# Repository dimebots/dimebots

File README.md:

Dimebots are a collection of autonomous and self-contained micro-robots that are as small as a dime and weigh less than a nickel, making Dimebots some of the smallest robots in the world. 

<p><strong>Microchip/Atmel ATTiny1614 &amp; Texas Instruments DRV8837</strong></p>

<p>The search for a suitable microcontroller is constrained by a number 
of factors. These factors included providing the necessary peripherals 
that are required, such as <a href="https://en.wikipedia.org/wiki/Pulse-width_modulation" target="_blank" rel="noreferrer noopener">Pulse Width Modulation (PWM)</a>, at least one <a href="https://en.wikipedia.org/wiki/Universal_asynchronous_receiver-transmitter" target="_blank" rel="noreferrer noopener">Universal Asynchronous Receiver/Transmitter (UART)</a>, support for at least one Inter-Integrated Circuit <a href="https://en.wikipedia.org/wiki/I%C2%B2C" target="_blank" rel="noreferrer noopener">(I²C)</a> communication bus, and in-circuit serial programming <a href="https://ww1.microchip.com/downloads/en/DeviceDoc/30277d.pdf" target="_blank" rel="noreferrer noopener">(ICSP)</a>. I originally designed the Dimebots to utilized the 8-bit <a href="https://www.microchip.com/en-us/product/ATmega328P" target="_blank" rel="noreferrer noopener">Microchip/Atmel ATmega328p</a> which is the microcontroller found in the <a href="https://www.arduino.cc/" target="_blank" rel="noreferrer noopener">Arduino Uno</a>.
 The ATmega328p provides a simple and easy-to-understand coding platform
 through the Arduino integrated development environment (IDE) while also
 coming in a number of footprints that could work for my requirements, 
namely a 32 pin <a href="https://en.wikipedia.org/wiki/Quad_flat_package" target="_blank" rel="noreferrer noopener">Thin Quad Flat Package (TQFP)</a> and 28 and 32 pin <a href="https://en.wikipedia.org/wiki/Flat_no-leads_package" target="_blank" rel="noreferrer noopener">Very Thin Plastic Quad Flat No-Lead (VQFN)</a>. I went as far as laying out an <a href="https://www.microchip.com/en-us/product/ATmega328P" target="_blank" rel="noreferrer noopener">ATMega328p</a>
 using a VQFN footprint, but the additional support requirements of 
using the ATMega328p such as a 6 pin ICSP header and an external 8MHz 
crystal/resonator necessitated a smaller microcontroller. In addition, 
the great dearth of microchips because of the COVID-19 pandemic 
disrupting global supply chains, stay-at-home orders increasing, and 
demand for consumer electronics and electric vehicle adoption, such as 
the ATMega328p, makes my selection of a suitable microcontroller much 
narrower. I decided to give myself a couple of weeks to see if I could 
nail down a microcontroller that is small, yet peripheral rich. 
Fortunately, <a href="https://github.com/SpenceKonde/megaTinyCore" target="_blank" rel="noreferrer noopener">Spence Konde (aka Dr. Azzy)</a>
 had recently released Arduino support for the newer microcontrollers 
offered by Microchip/Atmel, including support for the tinyAVR 2-Series, 
the tinyAVR 1-Series, and the tinyAVR 0-Series of chips. After testing a
 number of different microcontrollers, I chose the <a href="https://www.microchip.com/en-us/product/ATTINY1614" target="_blank" rel="noreferrer noopener">ATTiny1614</a> in a 14-pin <a href="https://en.wikipedia.org/wiki/Small_outline_integrated_circuit" target="_blank" rel="noreferrer noopener">Small Outline Integrated Circuit (SOIC)</a>
 footprint due to its necessary peripherals, overall microcontroller 
size and footprint, and most importantly, its availability. The 
ATTiny1614 can be powered by a wide variety of voltages including 1.8V 
all the way up to 5.5, has multiple I²C buses and multiple UART’s, has 6
 PWM channels, and used the <a href="https://onlinedocs.microchip.com/pr/GUID-DDB0017E-84E3-4E77-AAE9-7AC4290E5E8B-en-US-4/index.html?GUID-9B349315-2842-4189-B88C-49F4E1055D7F" target="_blank" rel="noreferrer noopener">Unified Program and Debug Interface (UPDI)</a>
 for programming. The UPDI interface is perfect for my needs, as it 
required only a 3-pin programming interface versus the 6-pin interface 
used for the ATMega328p.</p>

<p>The <a href="https://www.ti.com/product/DRV8837" target="_blank" rel="noreferrer noopener">Texas Instruments DRV8837</a>
 is chosen as the motor driver for the Dimebots. The DRV8837 output 
driver block consists of N-channel power MOSFETs configured as an 
H-bridge to drive the motor winding. An internal charge pump generates 
needed gate drive voltages. The Texas Instruments DRV8837 is packaged 
with a host of features, namely:</p>

<ul>
<li>1.8-A Maximum Drive Current</li>
<li>Separate Motor and Logic Supply Pins</li>
<li>Motor VM: 0 to 11 V</li>
<li>Logic VCC: 1.8 to 7 V</li>
<li>PWM Interface with IN1 and IN2 receiving PWM input</li>
<li>Low-Power Sleep Mode With 120-nA Maximum Sleep Current</li>
<li>nSLEEP pin</li>
<li>Small Footprint – 8-Pin WSON With Thermal Pad with a 2.0mm × 2.0mm size</li>
</u!>

<p><strong>Vishay VCNL4040 Proximity Sensor</strong></p>

<p>I sampled and tested numerous proximity sensors to find one that is power friendly, small, and available. This included sensors such as the Broadcom APDS-9960, the ON Semiconductor QRE1113, and the Sharp GP2S60. I finally selected the VCNL4040 from Vishay that interfaced with the ATTiny1614 using the I²C protocol.</p>

<p><strong>Nanjing Qinheng Microelectronics CH9141 Bluetooth (BLE4.2) Module</strong></p>

<p>Searching for a Bluetooth LE module that is tiny enough to fit the constraints of the robots mainboard while also providing for some type of serial communications is a challenge. All of the traditional Bluetooth 2.0 Serial Port Profile (SPP) modules were either too large or too power hungry to meet the dime-sized requirements of the Dimebots. After a few weeks of exhaustive searching, I discovered the CH9141. The CH9141 module ticked all of the requirements I needed, including:</p>
<ul>
   <li> Supporting the standard Bluetooth V4.2 protocol</li>
   <li> Bluetooth transmission distance up to 100 meters</li>
   <li> Two-way transparent transmission of serial port and Bluetooth data</li>
   <li> Support Bluetooth broadcast, host, and slave modes</li>
   <li> Support serial port AT command configuration</li>
   <li> Serial port baud rate supporting 300bps all the way up to 921600bps</li>
   <li> Support for adjustable serial port parameters</li>
</ul>
<p>The CH9141 module integrates master and slave functionality, while being configured through AT serial commands. The serial AT commands were used for configuring the CH9141 module to set the modules device name, module password, and serial baud rate to 9600bps.</p>

<p><strong>Microchip MCP1700 Low Dropout (LDO) Voltage Regulator</strong></p>

<p>A source of a stable and clean 3.3V is needed to power the dimebot and its peripherals. The Microchip MCP1700 Low Dropout (LDO) Voltage Regulator is a CMOS low dropout positive voltage regulator which can source up to 250mA of current with an extremely low input-output voltage differential of 178mV at 250mA. The low dropout voltage combined with the low current consumption of only 1.6µA makes this part ideal for battery operation. The low voltage differential (dropout voltage) extends battery operating lifetime. The MCP1700 is stable with 1.0µF ceramic output capacitor. It also permits high currents in small packages when operated with minimum VIN – VOUT differentials. The circuit also incorporates short-circuit protection & over temperature protection to ensure maximum reliability.</p>

<p><strong>Microchip MCP73831 Linear Charge Management Controller</strong></p>

<p>The Microchip MCP73831 Linear Charge Management Controller is a tiny 500mA linear charge management controller which includes integrated a pass transistor, integrated current sensing, and reverse discharge protection in 5-pin SOT-23 and thermally-efficient 8-pin 2mm x 3mm Dual-Flat No-Leads (DFN) package. Additionally, the Microchip MCP73831 features:</p>
<ul>
    <li>High accuracy preset output voltage regulation (+/-0.75%)</li>
    <li>User-programmable charge current</li>
    <li>Charge status output can directly drive LEDs</li>
    <li>On-chip thermal regulation</li>
    <li>Preconditioning and end-of-charge ratio options</li>
    <li>Under-voltage lockout</li>
</ul>
<p>The MCP73831 device is a highly advanced linear charge management controllers for use in space-limited, cost-sensitive applications.</p>

<p><strong>3.7V 30mAh Rechargeable Lithium Polymer (LiPo) Battery</strong></p>

<p>The main factor that ultimately determined the size of the robot (and most every robot in the world) is the size of the battery. The balancing act between battery size and power is challenging to say the least. On one hand, I needed something that fit in the dimensions of the robot. On the other hand, I needed a battery that provided enough voltage and amperage to run the robot and its associated peripherals, while ensuring a robot runtime that is acceptable. The battery chosen is a 3.7V 30mAh Rechargeable LiPo Battery.</p>

<p><strong>Motor – 4mm x 8mm Pager Motor</strong></p>
<p>The 4mm x 8mm pager motors used are coreless motors with a .70mm shaft diameter. Manufacturer test data states that these motors run at:</p>
<ul>
  <li>1.5V 18000RPM 5mA</li>
<li>3.0V 37000RPM 8mA</li>
 <li>3.7V 47000RPM 10mA</li>
 <li>5.0V 62000RPM 25mA</li>
</ul>

</body></html>

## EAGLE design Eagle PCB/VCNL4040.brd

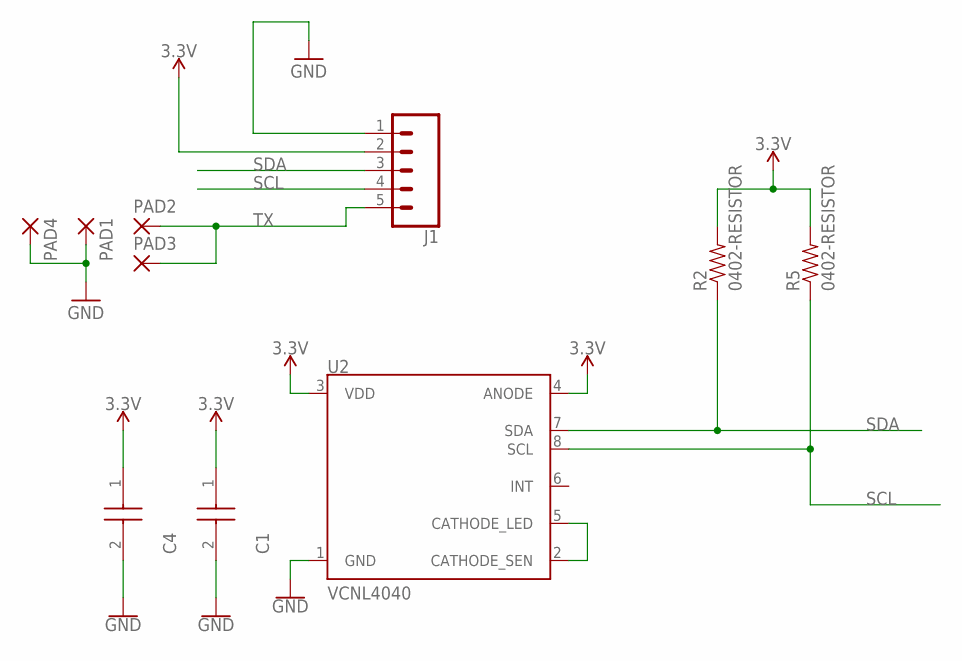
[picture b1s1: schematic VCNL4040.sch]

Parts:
C1, C4: 0402-CAPCAPACITOR-0402; CAPC1005X56N
J1: CONN_051.27MM; 1X05_1.27MM
PAD1, PAD2, PAD3, PAD4: SMD2; SMD1,27-2,54
R2, R5: 0402-RESISTOR; 0402
U2: VCNL4040; SPARKX_VCNL4040

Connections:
3.3V: C1.1, C4.1, J1.2, R2.2, R5.2, U2.3 (VDD), U2.4 (ANODE)
GND: C1.2, C4.2, J1.1, PAD1.1, PAD4.1, U2.1 (GND)
unnamed: U2.2 (CATHODE_SEN), U2.5 (CATHODE_LED)
SCL: J1.4, R5.1, U2.8 (SCL)
SDA: J1.3, R2.1, U2.7 (SDA)
TX: J1.5, PAD2.1, PAD3.1

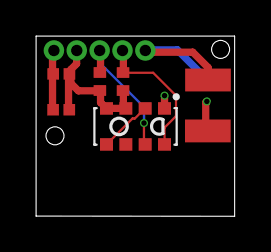
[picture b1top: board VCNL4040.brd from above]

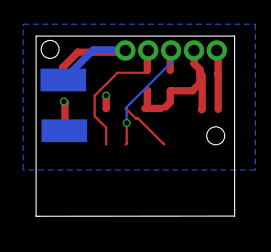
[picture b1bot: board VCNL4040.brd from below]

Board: 2 copper layers, 11.0 x 10.0 mm, 10 parts (2 on the bottom side), 6 nets.

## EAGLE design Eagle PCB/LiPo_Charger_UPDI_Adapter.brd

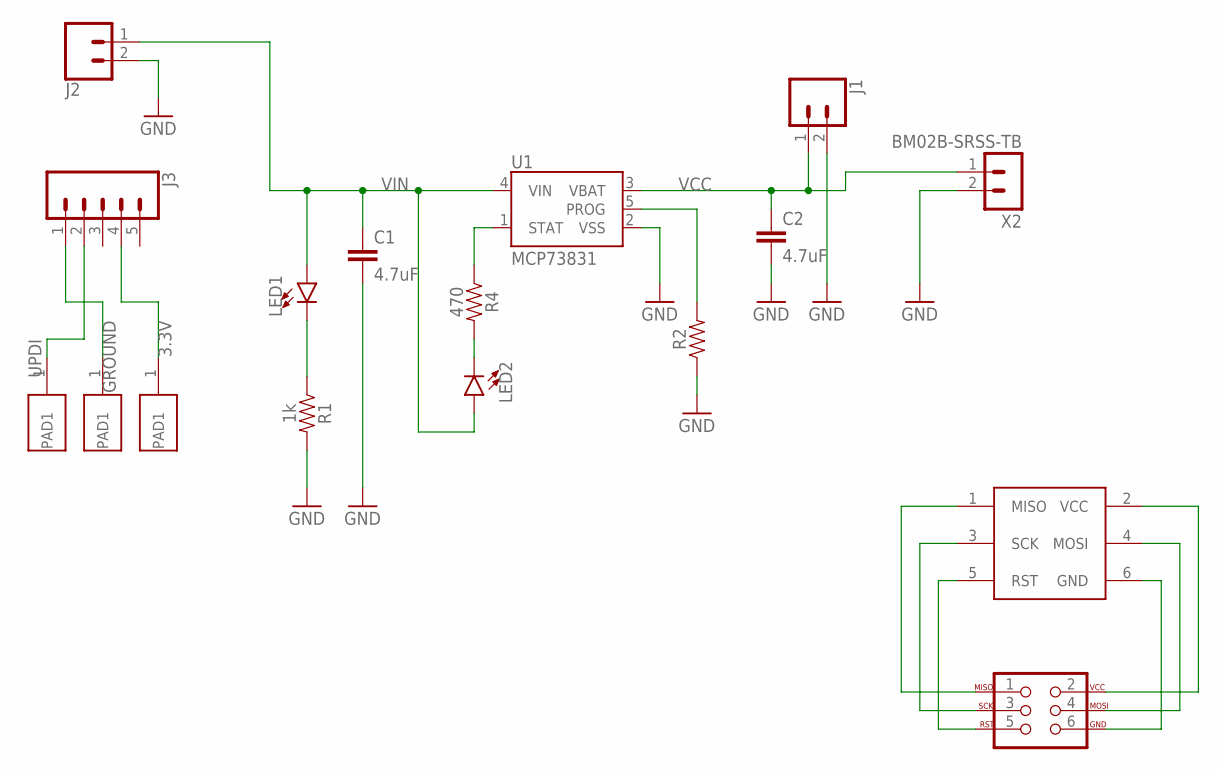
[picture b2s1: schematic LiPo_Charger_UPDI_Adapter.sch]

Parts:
C1, C2: 4.7uF; 1206
J1, J2: CONN_02; 1X02
J3: CONN_05; 1X05
J4: AVR_SPI_PROG_3X2NS; 2X3-NS
LED1, LED2: LED-FKIT-1206; FKIT-LED-1206
R1: 1k; 1206
R2: AXIAL-0.3
R4: 470; 1206
U1: MCP73831; SOT23-5
U$1, U$2, U$3: SINGLE_1.27MM_HOLE; 1.27MM_SINGLE_HOLE
U$4: 2X3_1.27MM_ICSP
X2: BM02B-SRSS-TB

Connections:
3.3V: J3.4, U$3.1
GND: C1.2, C2.2, J1.2, J2.2, R1.2, R2.P$1 (1), U1.2 (VSS), X2.2
GROUND: J3.1, U$2.1
unnamed: LED1.C, R1.1
unnamed: LED2.C, R4.2
unnamed: J4.1, U$4.1 (MISO)
unnamed: J4.3, U$4.3 (SCK)
unnamed: J4.5, U$4.5 (RST)
unnamed: J4.6, U$4.6 (GND)
unnamed: J4.4, U$4.4 (MOSI)
unnamed: J4.2, U$4.2 (VCC)
PROG: R2.P$2 (2), U1.5 (PROG)
STAT: R4.1, U1.1 (STAT)
UPDI: J3.2, U$1.1
VCC: C2.1, J1.1, U1.3 (VBAT), X2.1
VIN: C1.1, J2.1, LED1.A, LED2.A, U1.4 (VIN)

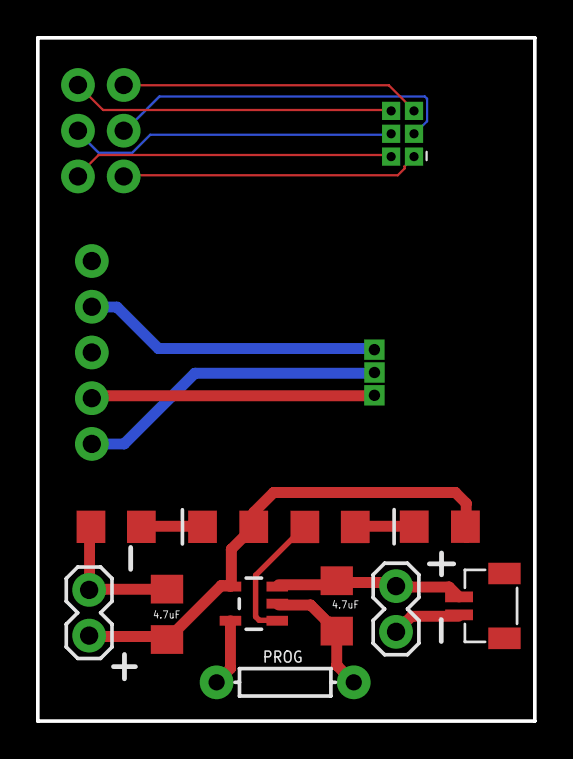
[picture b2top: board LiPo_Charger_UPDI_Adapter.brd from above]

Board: 2 copper layers, 27.6 x 38.0 mm, 17 parts (1 on the bottom side), 16 nets.

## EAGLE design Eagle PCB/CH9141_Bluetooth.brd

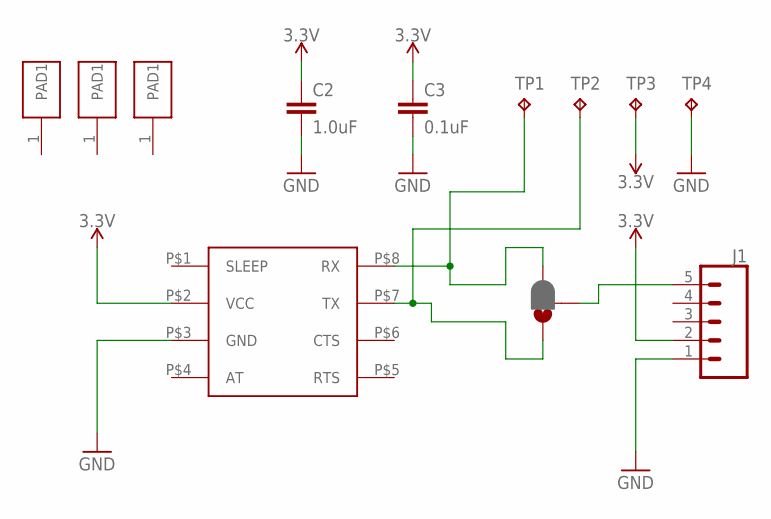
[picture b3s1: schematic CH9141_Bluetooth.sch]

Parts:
C2: 1.0uF; 0805
C3: 0.1uF; 0805
J1: CONN_051.27MM; 1X05_1.27MM
JP1: JUMPER-SMT_3_1-NC_PASTE_NO-SILK; SMT-JUMPER_3_1-NC_PASTE_NO-SILK
TP1, TP2, TP3, TP4: TPB2,54; B2,54
U$1: CH9141; CH9141_FOOTPRINT
U$2, U$3, U$4: SINGLE_1.27MM_HOLE; 1.27MM_SINGLE_HOLE

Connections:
3.3V: C2.1, C3.1, J1.2, TP3.TP, U$1.P$2 (VCC)
GND: C2.2, C3.2, J1.1, TP4.TP, U$1.P$3 (GND)
unnamed: JP1.3, TP1.TP, U$1.P$8 (RX)
unnamed: JP1.1, TP2.TP, U$1.P$7 (TX)
unnamed: J1.5, JP1.2

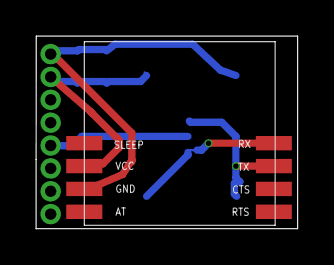
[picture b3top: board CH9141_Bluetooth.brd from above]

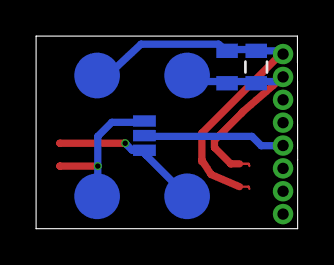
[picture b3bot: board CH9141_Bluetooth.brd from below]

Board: 2 copper layers, 14.5 x 10.7 mm, 12 parts (7 on the bottom side), 5 nets.

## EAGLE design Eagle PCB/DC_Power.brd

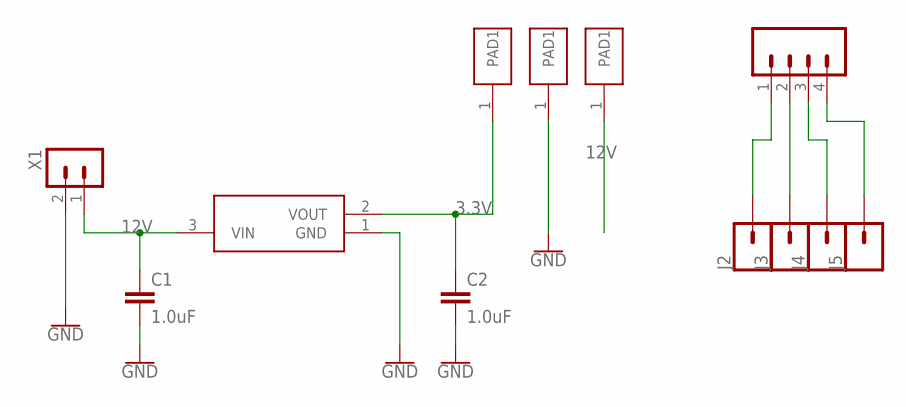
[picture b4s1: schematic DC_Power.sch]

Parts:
C1, C2: 1.0uF; 0805
IC1: MCP1700T-3302E_TT; SOT95P237X112-3N
J1: CONN_041.27MM; 1X04_1.27MM
J2, J3, J4, J5: CONN_01PTH_NO_SILK_YES_STOP; 1X01_NO_SILK
U$1, U$2, U$3: SINGLE_1.27MM_HOLE; 1.27MM_SINGLE_HOLE
X1: BM02B-SRSS-TB

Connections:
3.3V: C2.1, IC1.2 (VOUT), U$1.1
12V: C1.1, IC1.3 (VIN), U$3.1, X1.1
GND: C1.2, C2.2, IC1.1 (GND), U$2.1, X1.2
unnamed: J1.1, J2.1
unnamed: J1.2, J3.1
unnamed: J1.3, J4.1
unnamed: J1.4, J5.1

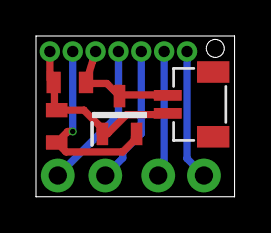
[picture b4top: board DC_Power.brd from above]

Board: 2 copper layers, 11.0 x 8.9 mm, 12 parts (0 on the bottom side), 7 nets.

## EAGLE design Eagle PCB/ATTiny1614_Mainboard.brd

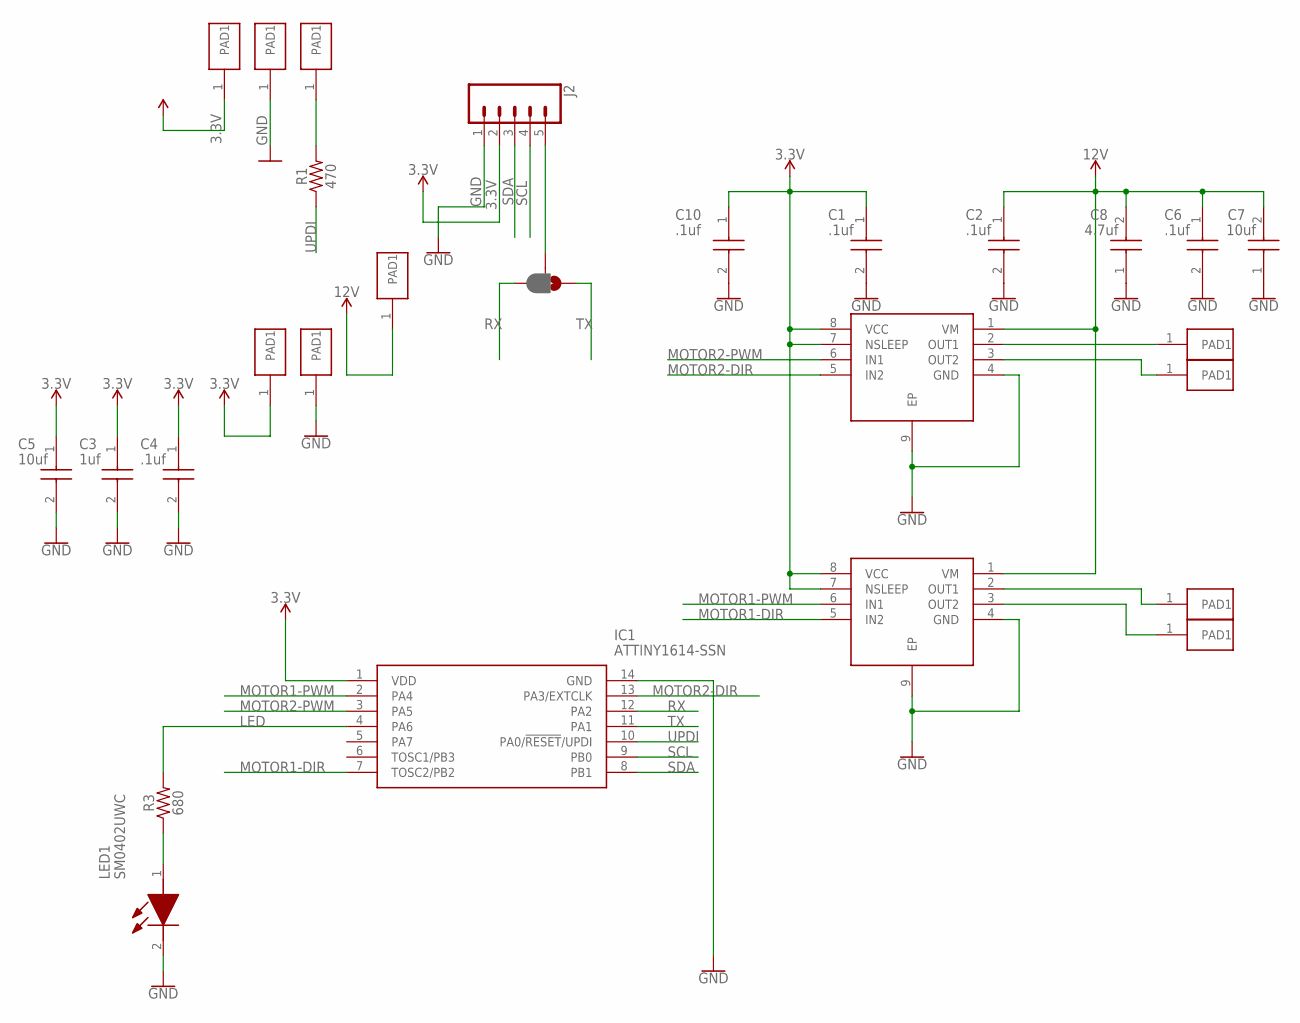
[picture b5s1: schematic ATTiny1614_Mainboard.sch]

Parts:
C1, C2, C4, C6, C10: .1uf; CAPC1005X56N
C3: 1uf; CAPC1005X56N
C5, C7: 10uf; CAPC1005X56N
C8: 4.7uf; CAPC1005X56N
IC1: ATTINY1614-SSN; SOIC127P600X175-14N
IC2, IC3: DRV8837DSGR; SON50P200X200X80-9N
J2: CONN_051.27MM; 1X05_1.27MM
JP1: JUMPER-SMT_3_1-NC_PASTE_NO-SILK; SMT-JUMPER_3_1-NC_PASTE_NO-SILK
LED1: SM0402UWC
R1: 470; 0402
R3: 680; 0402
U$1, U$2, U$3, U$4, U$5, U$6, U$7, U$8, U$9, U$12: SINGLE_1.27MM_HOLE; 1.27MM_SINGLE_HOLE

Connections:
3.3V: C1.1, C3.1, C4.1, C5.1, C10.1, IC1.1 (VDD), IC2.7 (NSLEEP), IC2.8 (VCC), IC3.7 (NSLEEP), IC3.8 (VCC), J2.2, U$1.1, U$4.1
12V: C2.1, C6.1, C7.2, C8.2, IC2.1 (VM), IC3.1 (VM), U$12.1
GND: C1.2, C2.2, C3.2, C4.2, C5.2, C6.2, C7.1, C8.1, C10.2, IC1.14 (GND), IC2.4 (GND), IC2.9 (EP), IC3.4 (GND), IC3.9 (EP), J2.1, LED1.2 (K), U$2.1, U$3.1
LED: IC1.4 (PA6), R3.2
MOTOR1-DIR: IC1.7 (TOSC2/PB2), IC2.5 (IN2)
MOTOR1-PWM: IC1.2 (PA4), IC2.6 (IN1)
MOTOR2-DIR: IC1.13 (PA3/EXTCLK), IC3.5 (IN2)
MOTOR2-PWM: IC1.3 (PA5), IC3.6 (IN1)
unnamed: IC2.2 (OUT1), U$8.1
unnamed: IC2.3 (OUT2), U$9.1
unnamed: IC3.2 (OUT1), U$6.1
unnamed: IC3.3 (OUT2), U$7.1
unnamed: LED1.1 (A), R3.1
unnamed: J2.5, JP1.2
unnamed: R1.2, U$5.1
RX: IC1.12 (PA2), JP1.3
SCL: IC1.9 (PB0), J2.4
SDA: IC1.8 (PB1), J2.3
TX: IC1.11 (PA1), JP1.1
UPDI: IC1.10 (PA0/!RESET!/UPDI), R1.1

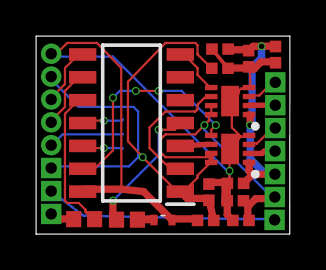
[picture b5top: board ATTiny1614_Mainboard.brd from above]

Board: 2 copper layers, 14.1 x 11.0 mm, 27 parts (1 on the bottom side), 20 nets.

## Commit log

2023-07-19 Create 1
2023-07-19 Create Eagle PCB
2023-07-19 Create Fusion 360
2023-07-19 Create sed

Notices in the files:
parts and their libraries:
SparkFun-Resistors: Licensing: Creative Commons ShareAlike 4.0 International - https://creativecommons.org/licenses/by-sa/4.0
SparkFun_newer: Licensing: CC v3.0 Share-Alike You are welcome to use this library for commercial purposes.
